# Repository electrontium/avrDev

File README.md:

avrDev
======

AVR-based boards, accessories, and code

This repo will hold Eagle files for my avr-based projects, arduino
sketches, sketchup files and the like.

I'll be linking to here quite often from blog.hovertop.com

-Tyler Harrison

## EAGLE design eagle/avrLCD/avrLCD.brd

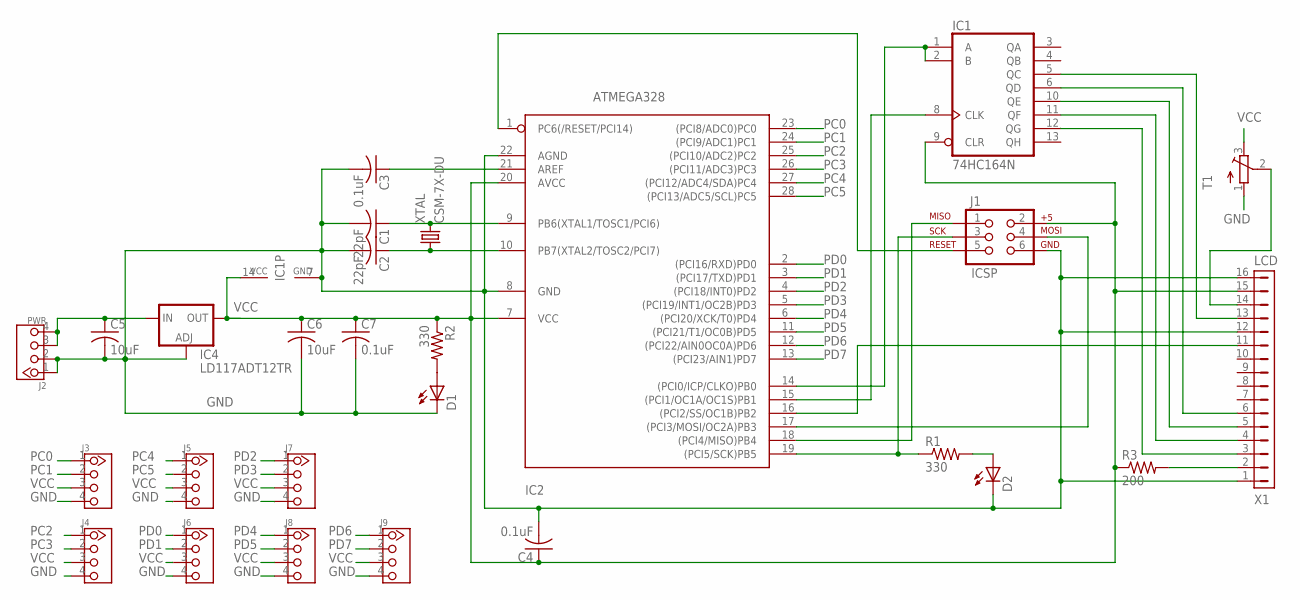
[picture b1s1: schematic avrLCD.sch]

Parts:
C1, C2: 22pF; C0805
C3, C4, C7: 0.1uF; C0805
C5, C6: 10uF; C1206
D1, D2: LEDCHIP-LED0805; CHIP-LED0805
IC1: 74HC164N; DIL14
IC2: ATMEGA328; DIL28-3
IC4: LD117ADT12TR; DPACK
J1: ICSP; 2X3-NS
J2: PWR; 4P-2.0
J3, J4, J5, J6, J7, J8, J9: TWIG-4P-2.0-2.0; 4P-2.0
R1, R2: 330; R0805
R3: 200; R1206
T1: TRIMPOTTC33X; TC33X
X1: LCD; FH21-16S-1DS
XTAL: CSM-7X-DU

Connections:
GND: C1.2, C2.2, C3.2, C4.2, C5.2, C6.2, C7.2, D1.C, D2.C, IC1.7 (GND), IC2.8 (GND), IC2.22 (AGND), IC4.1 (ADJ), J1.6, J2.1, J2.2, J3.4, J4.4, J5.4, J6.4, J7.4, J8.4, J9.4, T1.1 (A), X1.1, X1.12, X1.16
unnamed: IC2.17 ((PCI3/MOSI/OC2A)PB3), J1.4
unnamed: IC2.18 ((PCI4/MISO)PB4), J1.1
unnamed: IC2.19 ((PCI5/SCK)PB5), J1.3, R1.1
unnamed: IC2.1 (PC6(/RESET/PCI14)), J1.5
unnamed: R3.2, X1.2
unnamed: C1.1, IC2.9 (PB6(XTAL1/TOSC1/PCI6)), XTAL.2
unnamed: C2.1, IC2.10 (PB7(XTAL2/TOSC2/PCI7)), XTAL.1
unnamed: C3.1, IC2.21 (AREF)
unnamed: D2.A, R1.2
unnamed: IC1.1 (A), IC1.2 (B), IC2.14 ((PCI0/ICP/CLKO)PB0)
unnamed: C5.1, IC4.3 (IN), J2.3, J2.4
unnamed: D1.A, R2.2
unnamed: IC1.8 (CLK), IC2.15 ((PCI1/OC1A/OC1S)PB1)
unnamed: IC1.5 (QC), X1.13
unnamed: IC2.16 ((PCI2/SS/OC1B)PB2), X1.11
unnamed: IC1.6 (QD), X1.6
unnamed: IC1.10 (QE), X1.5
unnamed: IC1.11 (QF), X1.4
unnamed: IC1.12 (QG), X1.3
unnamed: T1.2 (S), X1.14
PC0: IC2.23 ((PCI8/ADC0)PC0), J3.1
PC1: IC2.24 ((PCI9/ADC1)PC1), J3.2
PC2: IC2.25 ((PCI10/ADC2)PC2), J4.1
PC3: IC2.26 ((PCI11/ADC3)PC3), J4.2
PC4: IC2.27 ((PCI12/ADC4/SDA)PC4), J5.1
PC5: IC2.28 ((PCI13/ADC5/SCL)PC5), J5.2
PD0: IC2.2 ((PCI16/RXD)PD0), J6.1
PD1: IC2.3 ((PCI17/TXD)PD1), J6.2
PD2: IC2.4 ((PCI18/INT0)PD2), J7.1
PD3: IC2.5 ((PCI19/INT1/OC2B)PD3), J7.2
PD4: IC2.6 ((PCI20/XCK/T0)PD4), J8.1
PD5: IC2.11 ((PCI21/T1/OC0B)PD5), J8.2
PD6: IC2.12 ((PCI22/AIN0OC0A)PD6), J9.1
PD7: IC2.13 ((PCI23/AIN1)PD7), J9.2
VCC: C4.1, C6.1, C7.1, IC1.9 (CLR), IC1.14 (VCC), IC2.7 (VCC), IC2.20 (AVCC), IC4.4 (OUT), J1.2, J3.3, J4.3, J5.3, J6.3, J7.3, J8.3, J9.3, R2.1, R3.1, T1.3 (E), X1.15

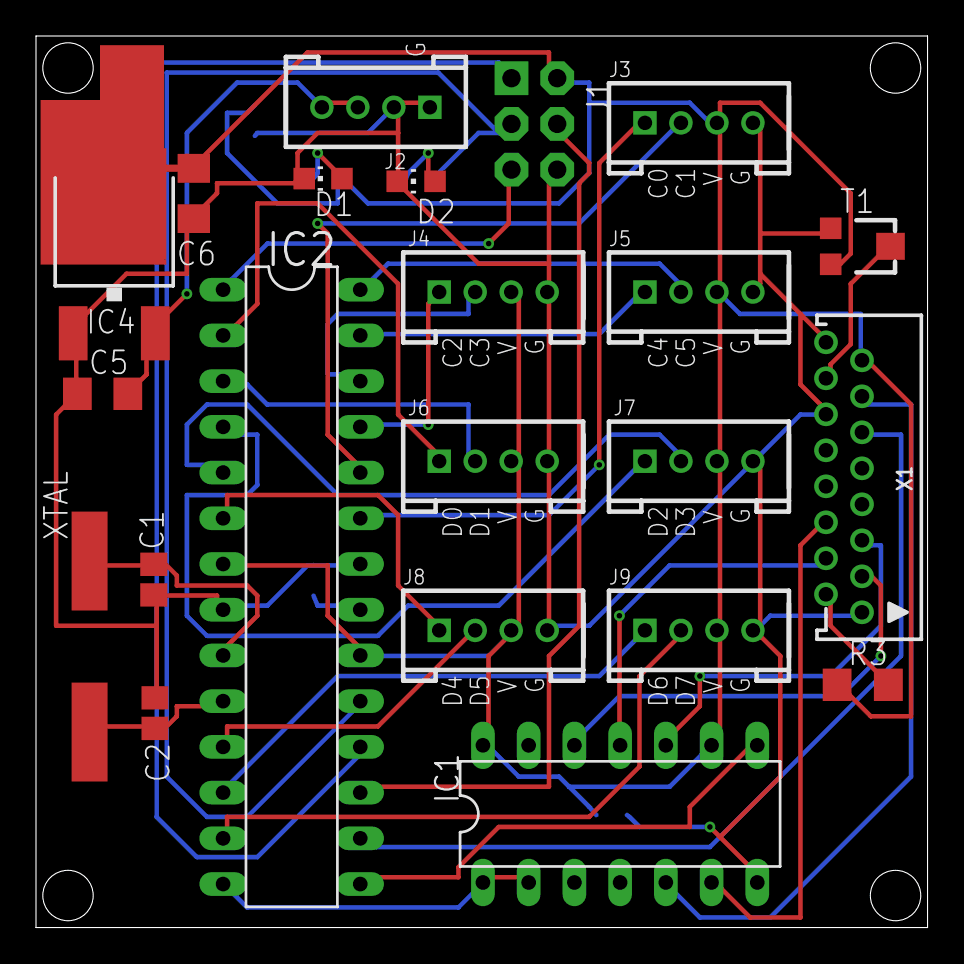
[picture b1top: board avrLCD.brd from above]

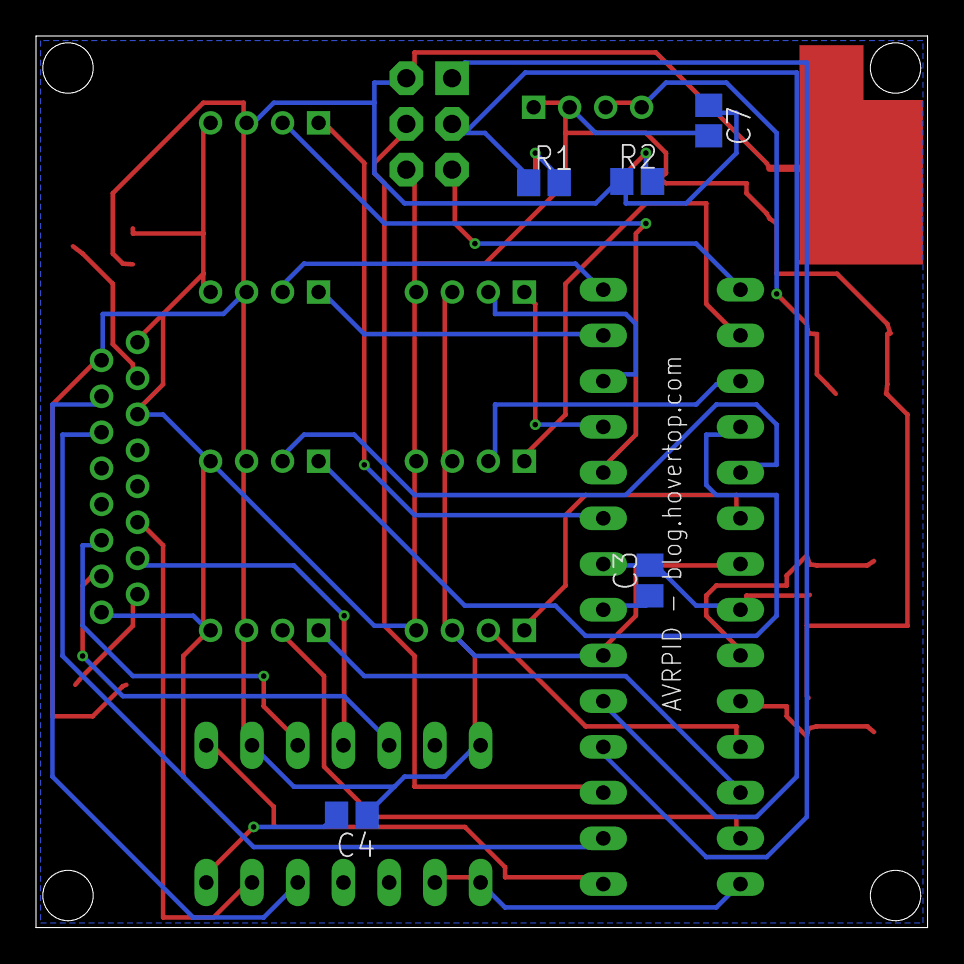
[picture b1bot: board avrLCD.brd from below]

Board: 2 copper layers, 49.5 x 49.5 mm, 27 parts (5 on the bottom side), 36 nets.

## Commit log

2013-02-06 Modifying readme for test commit
2013-02-06 Adding some avrLCD eagle files

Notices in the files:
parts and their libraries:
SparkFun: Licensing: CC v3.0 Share-Alike You are welcome to use this library for commercial purposes.
